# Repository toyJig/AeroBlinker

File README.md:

# AeroBlinker
Custom PCB w/ KiCAD that reads Receiver Signals to control light flash patterns - Aeronautics Team.

Read [JOURNAL.md](https://github.com/toyJig/AeroBlinker/blob/main/JOURNAL.md) for the logged process!

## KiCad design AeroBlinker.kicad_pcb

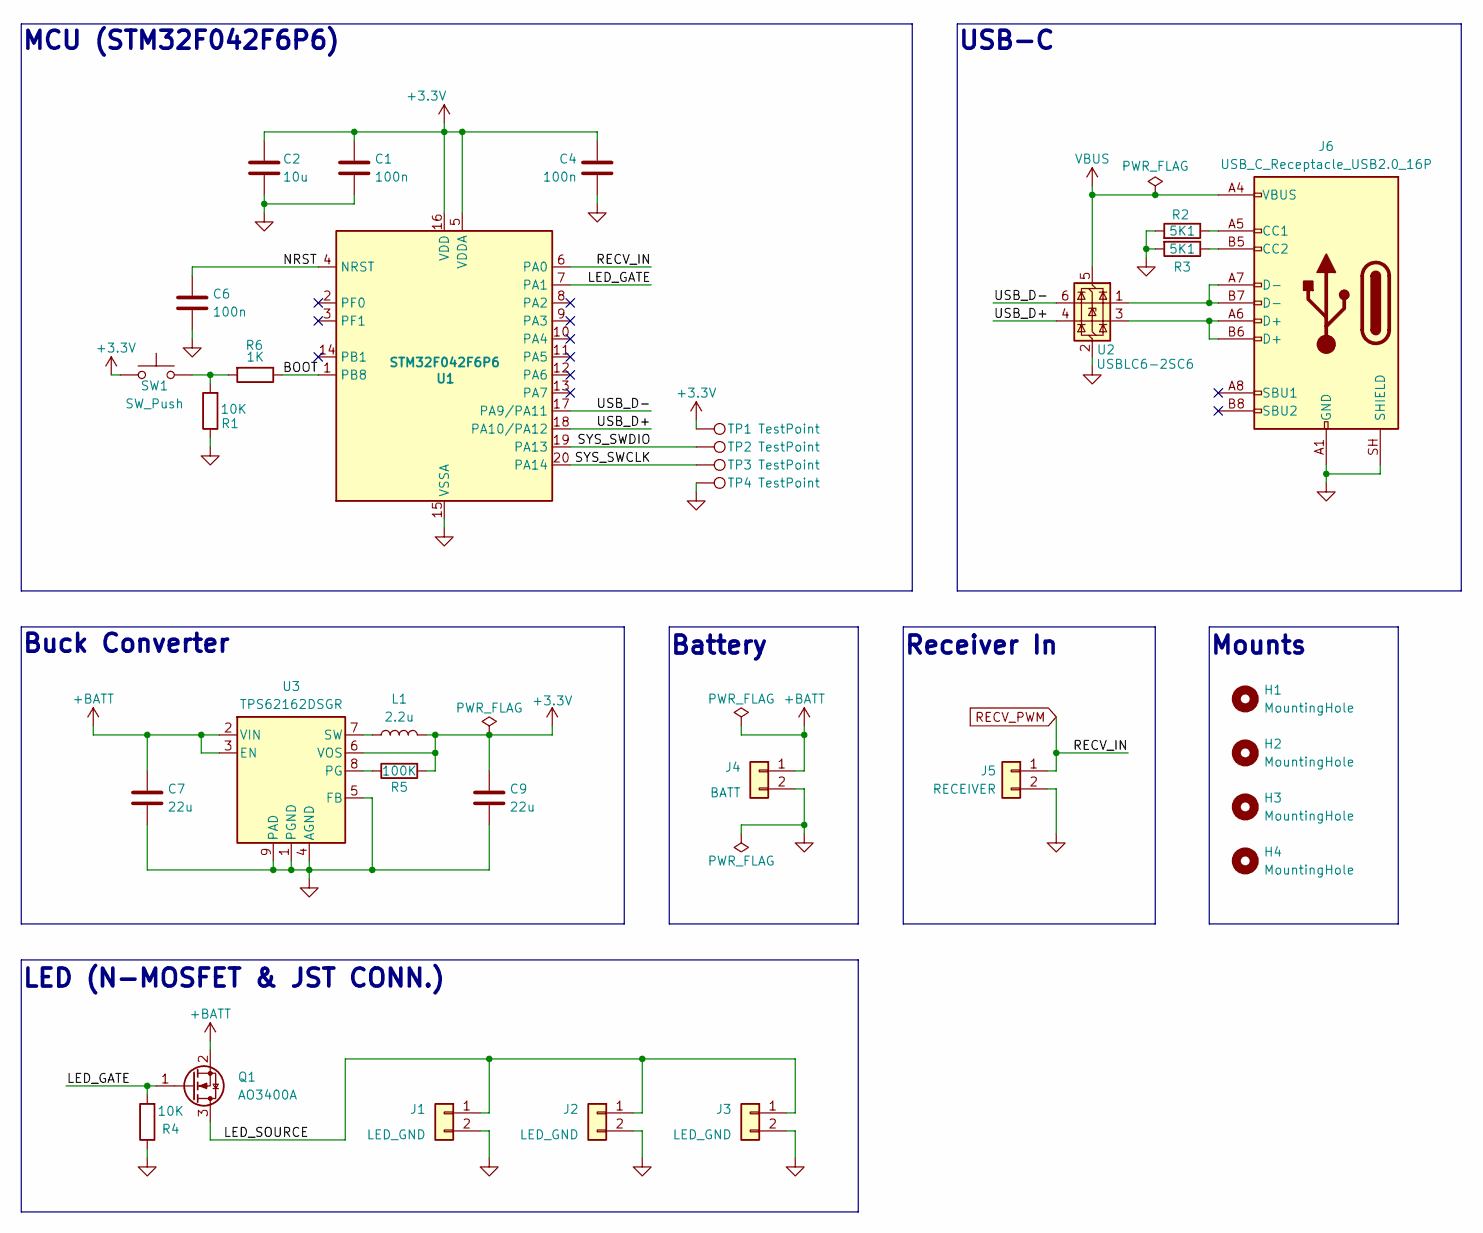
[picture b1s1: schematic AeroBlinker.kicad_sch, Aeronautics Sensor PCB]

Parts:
C1, C4, C6: 100n; C_0402_1005Metric; LCSC C1525
C2: 10u; C_0603_1608Metric; LCSC C19702
C7, C9: 22u; C_0603_1608Metric; LCSC C59461
H1, H2, H3, H4: MountingHole; MountingHole_2.1mm
J1, J2, J3: LED_GND; JST_XH_B2B-XH-A_1x02_P2.50mm_Vertical; LCSC C158012
J4: BATT; JST_VH_B2P-VH_1x02_P3.96mm_Vertical; LCSC C160315
J5: RECEIVER; JST_XH_B2B-XH-A_1x02_P2.50mm_Vertical; LCSC C158012
J6: USB_C_Receptacle_USB2.0_16P; USB_C_Receptacle_GCT_USB4105-xx-A_16P_TopMnt_Horizontal; LCSC C3025063
L1: 2.2u; L_Changjiang_FNR3015S; LCSC C167747
Q1: AO3400A; SOT-23; LCSC C20917
R1, R4: 10K; R_0402_1005Metric; LCSC C25744
R2, R3: 5K1; R_0402_1005Metric; LCSC C25905
R5: 100K; R_0603_1608Metric; LCSC C25803
R6: 1K; R_0402_1005Metric; LCSC C11702
SW1: SW_Push; SW_Push_1P1T_NO_CK_KMR2; LCSC C269272
TP1, TP2, TP3, TP4: TestPoint; TestPoint_Pad_1.5x1.5mm
U1: STM32F042F6P6; TSSOP-20_4.4x6.5mm_P0.65mm; LCSC C81000
U2: USBLC6-2SC6; SOT-23-6; LCSC C2827654
U3: TPS62162DSGR; Texas_DSG0008A_WSON-8-1EP_2x2mm_P0.5mm_EP0.9x1.6mm; LCSC C40256

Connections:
+3.3V: C1.1, C2.1, C4.1, C9.1, L1.2, R5.2, SW1.1, TP1.1 (1_1), U1.5 (VDDA), U1.16 (VDD), U3.6 (VOS); also elsewhere on the board
+BATT: C7.1, J4.1, Q1.2 (S), U3.2 (VIN), U3.3 (EN)
/BOOT: R6.1, U1.1 (PB8)
/LED_GATE: Q1.1 (G), R4.2, U1.7 (PA1)
/LED_SOURCE: J1.1, J2.1, J3.1, Q1.3 (D)
/NRST: C6.1, U1.4 (NRST)
/SYS_SWCLK: TP3.1 (1_1), U1.20 (PA14)
/SYS_SWDIO: TP2.1 (1_1), U1.19 (PA13)
/USB_D+: U1.18 (PA10/PA12), U2.4 (I/O2)
/USB_D-: U1.17 (PA9/PA11), U2.6 (I/O1)
GND: C1.2, C2.2, C4.2, C6.2, C7.2, C9.2, J1.2, J2.2, J3.2, J4.2, J5.2, J6.A1 (GND), J6.A12 (GND), J6.B1 (GND), J6.B12 (GND), J6.SH (SHIELD), R1.1, R2.2, R3.2, R4.1, TP4.1 (1_1), U1.15 (VSSA), U2.2 (GND), U3.1 (PGND), U3.4 (AGND), U3.5 (FB), U3.9 (PAD)
unnamed: J6.A5 (CC1), R2.1
unnamed: J6.B5 (CC2), R3.1
unnamed: J6.A6 (D+), J6.B6 (D+), U2.3 (I/O2)
unnamed: J6.A7 (D-), J6.B7 (D-), U2.1 (I/O1)
unnamed 15: R1.2, R6.2, SW1.2; also elsewhere on the board
unnamed: R5.1, U3.8 (PG)
unnamed: L1.1, U3.7 (SW)
RECV_PWM: J5.1, U1.6 (PA0)
VBUS: J6.A4 (VBUS), J6.A9 (VBUS), J6.B4 (VBUS), J6.B9 (VBUS), U2.5 (VBUS)

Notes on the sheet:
USB-C
LED (N-MOSFET & JST CONN.)
Buck Converter
Battery
Mounts
MCU (STM32F042F6P6)
Receiver In

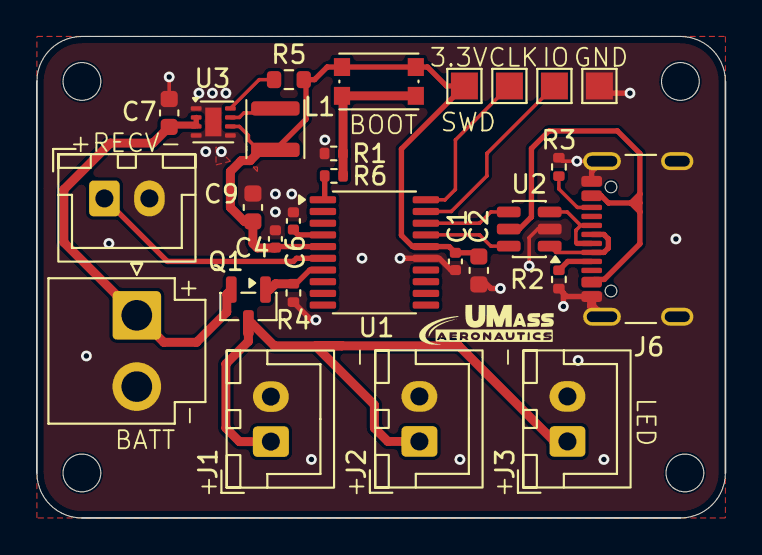
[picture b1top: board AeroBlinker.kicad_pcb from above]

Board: 2 copper layers, 38.2 x 26.8 mm, 32 parts (0 on the bottom side), 20 nets.

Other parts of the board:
SW2: SW_Push; SW_Push_1P1T_NO_CK_KMR2

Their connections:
+3.3V: SW2.1; also elsewhere on the board
unnamed 15: SW2.2; also elsewhere on the board

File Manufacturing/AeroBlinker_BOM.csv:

"Id";"Designator";"Footprint";"Quantity";"Designation";"Supplier and ref";
1;"C1, C4, C6";"C_0402_1005Metric";3;"100n";;;
2;"C2";"C_0603_1608Metric";1;"10u";;;
3;"C7, C9";"C_0603_1608Metric";2;"22u";;;
4;"D2";"SOT-23";1;"BZT585B3V3T-7";;;
5;"J1, J2, J3";"JST_XH_B2B-XH-A_1x02_P2.50mm_Vertical";3;"LED_GND";;;
6;"J4";"JST_VH_B2P-VH_1x02_P3.96mm_Vertical";1;"BATTERY";;;
7;"J5";"JST_XH_B2B-XH-A_1x02_P2.50mm_Vertical";1;"RECEIVER";;;
8;"J6";"USB_C_Receptacle_GCT_USB4105-xx-A_16P_TopMnt_Horizontal";1;"USB_C_Receptacle_USB2.0_16P";;;
9;"L1";"L_Changjiang_FNR3012S";1;"2.2u";;;
10;"Q1";"SOT-23";1;"AO3400A";;;
11;"R1, R4";"R_0402_1005Metric";2;"10K";;;
12;"R2";"R_0402_1005Metric";1;"5K";;;
13;"R3";"R_0603_1608Metric";1;"5K";;;
14;"R5";"R_0603_1608Metric";1;"100K";;;
15;"R6";"R_0402_1005Metric";1;"1K";;;
16;"SW2";"SW_Push_1P1T_NO_CK_KMR2";1;"SW_Push";;;
17;"TP1, TP2, TP3, TP4";"TestPoint_Pad_1.5x1.5mm";4;"TestPoint";;;
18;"U1";"TSSOP-20_4.4x6.5mm_P0.65mm";1;"STM32F042F6Px";;;
19;"U2";"SOT-23-6";1;"USBLC6-2SC6";;;
20;"U3";"Texas_DSG0008A_WSON-8-1EP_2x2mm_P0.5mm_EP0.9x1.6mm";1;"TPS62162DGR";;;
